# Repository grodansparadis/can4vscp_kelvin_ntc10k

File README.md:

-----

This project is part of the <a href="http://www.vscp.org">VSCP (Very Simple Control Protocol) project</a>. 

<hr>

# Kelvin NTC10K

This module is part of the [VSCP project](https://www.vscp.org).  It is free to use, modify and sell. The only thing we kindly ask is that improvements and extensions are contributed back to the project (at your will). This to make the project better for everyone. All design files is licensed under the [MIT license](https://en.wikipedia.org/wiki/MIT_License).

The full documentation for the module can be found [here](http://grodansparadis.github.io/can4vscp_kelvin_ntc10k/#/).

In this repository you find all development files for the Kelvin NTC10K module. The project together with the [Paris Relay Module](https://github.com/grodansparadis/can4vscp_paris) is the main examples for a VSCP implemention on a Microchip 18F PIC device.

## Abstract

Kelvin NTC10K is a temperature module that can handle six temperature sensors. One internal and five external.

The Kelvin NTC10KA module measures temperature. It measures temperatures in a wide range (depending on what sensors are used) and can achieve 0.1C accuracy with calibration. It does so by allowing connection of up to five external NTC temperature sensors and by measuring the temperature on the surface of the module itself. The measured temperature can be reported to other CAN4VSCP modules or to one or several servers so it can be collected in a database or visualized and analyzed in a diagram. The accuracy of the sensors can be increase further by calibration.

Temperature data can be presented by the module in Kelvin, Celsius or Fahrenheit.

Temperatures is reported automatically and it is possible to set alarms for high/low levels. Absolute low and high temperatures are collected and it is easy to construct autonomous and reliable temperature regulation systems.

NTC sensors has the advantage of being low cost, possible to get high accuracy from and ease of use with long cable runs. No calibration is usually needed if +-1 degree accuracy is OK.

The module fully adopts to the CAN4VSCP specification and can be powered directly over the bus with a 9-28V DC power source. It has a rich register set for configuration and any information events defined. It also have a decision matrix for easy dynamic event handling.

VSCP CAN modules are designed to work on a CAN4CAN bus which use ordinary RJ-45 connectors and is powered with 9-28V DC over the same cable. This means there is no need for a separate power cable. All that is needed is a CAT5 or better twisted pair cable. Buss length can be a maximum of 500 meters with drops of maximum 24 meters length (up to a total of 120 meters). As for all CAN4VSCP modules the communication speed is fixed at 125 kbps.

All VSCP modules contains information of there own setup, manual, hardware version, manufacturer etc. You just ask the module for the information you need and you will get it. When they are started up they have a default functionality that often is all that is needed to get a working setup. If the module have something to report it will send you an event and if it is setup to react on a certain type of event it will do it's work when you send event(s) to it. 

---

## Project files

### User manual
  * [User Manual](https://grodansparadis.github.io/can4vscp_kelvin_ntc10k/#)

### Schematic, PCB, 3D files etc
  * [Schematics reversion A](https://raw.githubusercontent.com/grodansparadis/can4vscp_accra/refs/heads/master/eagle/accra_sch_rev_A.png)
 * Hardware design files is made in [KiCad](https://kicad.org) and can be found in the `kicad` directory. Valid from reversion B of the hardware.
   * Gerber files for PCB production can be found in the `gerber` directory (in the `kicad` folder).
 * Eagle schema and board files for reversion A and B can be found in the `eagle` directory. They are no longer actively updated.

 ### Firmware

 The firmware is developed in [MPLAB X IDE](https://www.microchip.com/mplab/mplab-x-ide) using the [XC8 compiler](https://www.microchip.com/mplab/compilers).

  * Binary release files is available [here](https://github.com/grodansparadis/can4vscp_kelvin_ntc10k/releases)

### MDF - Module Description File(s)
  * [MDF file version: 1.2.0 Release date: 2015-02-18](http://www.eurosource.se/ntc10KA_3.xml)
  * [MDF file version: 1.1.0 Release date: 2014-12-24](http://www.eurosource.se/ntc10KA_2.xml)
  * [MDF file version: 1.0.0 Release date: 2012-02-24](http://www.eurosource.se/ntc10KA_1.xml)

### Support
If you need support, please open an issue in the [GitHub repository](https://github.com/grodansparadis/can4vscp_kelvin_ntc10k/issues).

### Buy a ready made modules
You can buy a ready made module from [Grodans Paradis](http://www.grodansparadis.com).

### Project related links
  * [VSCP project](https://www.vscp.org)
  * [VSCP Documentation site](https://docs.vscp.org/)
  * [VSCP Wiki](https://github.com/grodansparadis/vscp/wiki)

## Steps you should go through to adopt this file for your own VSCP project.

  * The frequency for your system may be different. This will affect the CAN bit rate settings which are defined in the biginning of the can18f.c file. Here you also find the filter/mask  defines if you need to change these. Timer0 is used as a 1 ms timer for the VSCP functionality. You should adopt the timer reload value in the main.h file to your system.

  * The GUID (Glocal Unique ID) is defined in the beginning of vscp.c This number should be different for each piece of equiment you produce. Regard it is as the device serial number. It can be moved to EEPROM if that is found more convinient. In that case the vscp_rcv_readreg  procedure in vscp.c also has to be changed.

  * The device URL is defined in the beginning of the vscp.c file. This is an URL without the initial "http://" that should point to a XML file that give information about your piece of equipment.

  * The manufacturer id is also defined in the beginning of the vscp.c file. You can use this id in any way you like.

In addition to this you may use different pins for the INIT button (RC0 today) and the status LED (RC1) today. Changes affect the main interrupt vector.

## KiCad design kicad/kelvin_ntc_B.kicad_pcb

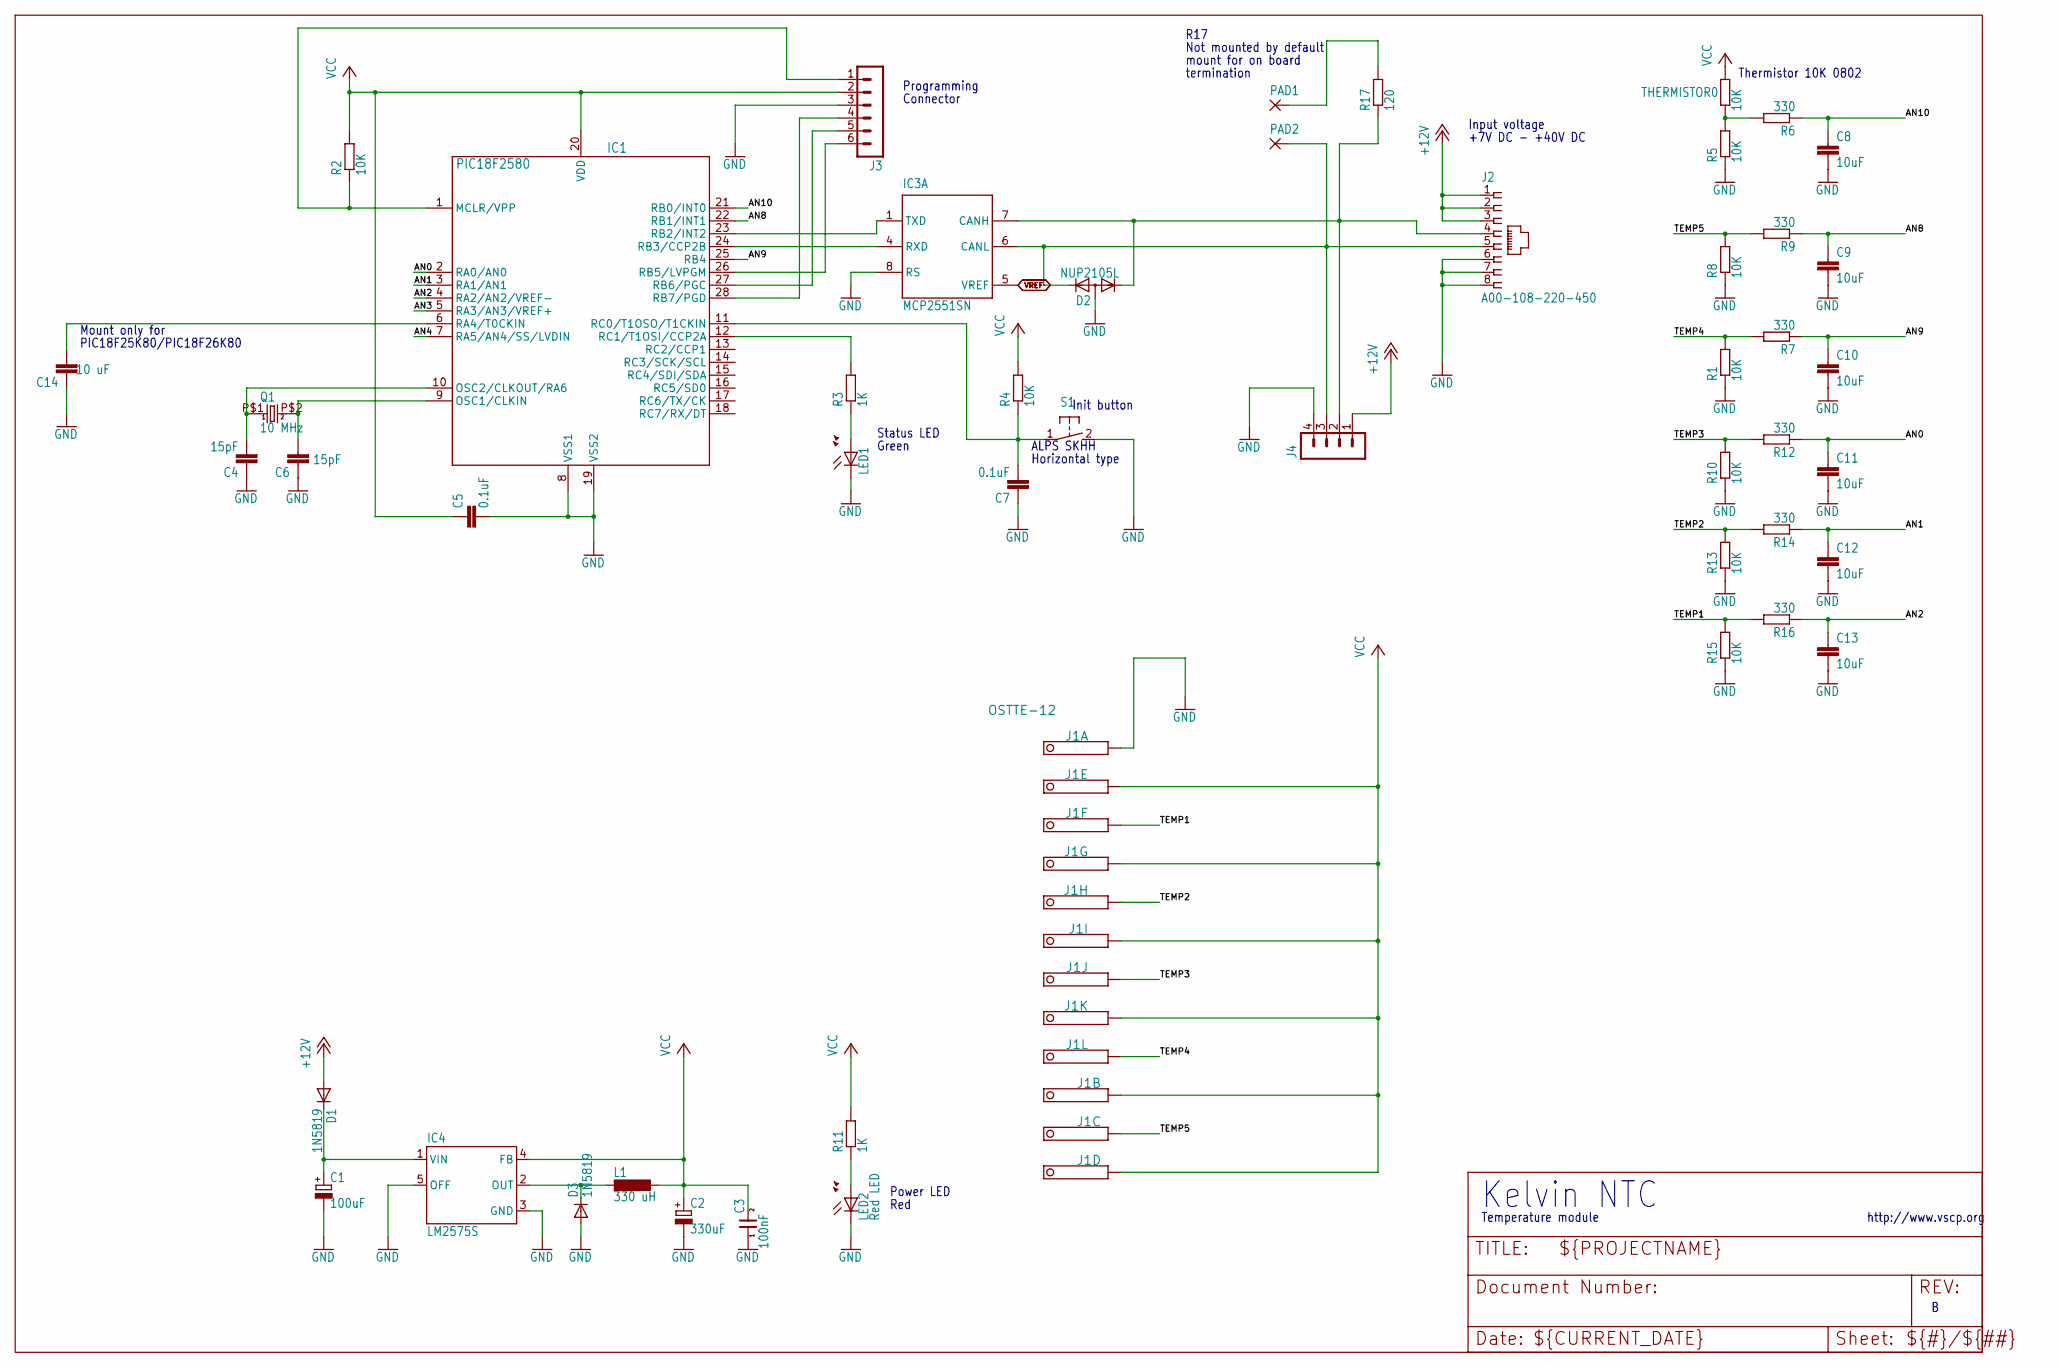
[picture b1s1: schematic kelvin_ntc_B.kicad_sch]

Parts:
C1: 100uF; PANASONIC_D
C2: 330uF; PANASONIC_D
C3: 100nF; 0805
C4, C6: 15pF; C0805
C5, C7: 0.1uF; C0805
C8, C9, C10, C11, C12, C13: 10uF; C0805
C14: 10 uF; C0805
D1, D3: 1N5819; SOD123
D2: NUP2105L; SOT23
IC1: PIC18F2580; SO28
IC3: MCP2551SN; SO-08
IC4: LM2575S; TO263-5
J1: OSTTE-12; PINHEAD-12
J2: A00-108-220-450; RJ-45
J3: MA06-1
J4: MA04-1
L1: 330 uH; DO3316P
LED1: LEDCHIP-LED0805; CHIP-LED0805
LED2: Red LED; CHIP-LED0805
PAD1, PAD2: 1,6/0,8; 1,6_0,8
Q1: 10 MHz; 9C
R1, R2, R4, R5, R8, R10, R13, R15: 10K; R0805
R3, R11: 1K; R0805
R6, R7, R9, R12, R14, R16: 330; R0805
R17: 120; R0805
S1: 31-XX; B3F-31XX
THERMISTOR0: 10K; R0805

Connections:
+12V: D1.A, J2.1, J2.2, J2.3, J4.1
AN0: C11.1, IC1.2 (RA0/AN0), R12.1
AN1: C12.1, IC1.3 (RA1/AN1), R14.1
AN2: C13.1, IC1.4 (RA2/AN2/VREF-), R16.1
AN3: IC1.5 (RA3/AN3/VREF+)
AN4: IC1.7 (RA5/AN4/SS/LVDIN)
AN8: C9.1, IC1.22 (RB1/INT1), R9.1
AN9: C10.1, IC1.25 (RB4), R7.1
AN10: C8.1, IC1.21 (RB0/INT0), R6.1
CANH: D2.1 (K1), IC3.7 (CANH), J2.4, J4.2, R17.1
CANL: D2.2 (K2), IC3.6 (CANL), J2.5, J4.3, PAD2.1
GND: C1.-, C2.-, C3.1, C4.1, C5.2, C6.1, C7.1, C8.2, C9.2, C10.2, C11.2, C12.2, C13.2, C14.1, D2.3 (A), D3.A, IC1.8 (VSS1), IC1.19 (VSS2), IC3.2 (VSS), IC3.8 (RS), IC4.3 (GND), IC4.5 (OFF), J1.1, J2.6, J2.7, J2.8, J3.3, J4.4, LED1.C, LED2.C, R1.1, R5.1, R8.1, R10.1, R13.1, R15.1, S1.2 (S)
unnamed: D3.C, IC4.2 (OUT), L1.1
unnamed: C4.2, IC1.10 (OSC2/CLKOUT/RA6), Q1.P$1 (1)
unnamed: C1.+, D1.C, IC4.1 (VIN)
unnamed: IC1.12 (RC1/T1OSI/CCP2A), R3.2
unnamed: LED1.A, R3.1
unnamed: C7.2, IC1.11 (RC0/T1OSO/T1CKIN), R4.1, S1.1
unnamed: C6.2, IC1.9 (OSC1/CLKIN), Q1.P$2 (2)
unnamed: R5.2, R6.2, THERMISTOR0.1
unnamed: C14.2, IC1.6 (RA4/T0CKIN)
unnamed: PAD1.1, R17.2
unnamed: IC1.1 (MCLR/VPP), J3.1, R2.1
unnamed: IC1.28 (RB7/PGD), J3.4
unnamed: IC1.27 (RB6/PGC), J3.5
unnamed: IC1.26 (RB5/LVPGM), J3.6
unnamed: LED2.A, R11.1
RXCAN: IC1.24 (RB3/CCP2B), IC3.4 (RXD)
TEMP1: J1.3, R15.2, R16.2
TEMP2: J1.5, R13.2, R14.2
TEMP3: J1.7, R10.2, R12.2
TEMP4: J1.9, R1.2, R7.2
TEMP5: J1.11, R8.2, R9.2
TXCAN: IC1.23 (RB2/INT2), IC3.1 (TXD)
VCC: C2.+, C3.2, C5.1, IC1.20 (VDD), IC3.3 (VDD), IC4.4 (FB), J1.2, J1.4, J1.6, J1.8, J1.10, J1.12, J3.2, L1.2, R2.2, R4.2, R11.2, THERMISTOR0.2
VREF: IC3.5 (VREF)

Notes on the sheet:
Init button
Connector
http://www.vscp.org
Mount only for
Input voltage
R17
Red
Thermistor 10K 0802
mount for on board
termination
Kelvin NTC
Horizontal type
Programming
Status LED
Not mounted by default
Power LED
+7V DC - +40V DC
Green
PIC18F25K80/PIC18F26K80
Temperature module
ALPS SKHH

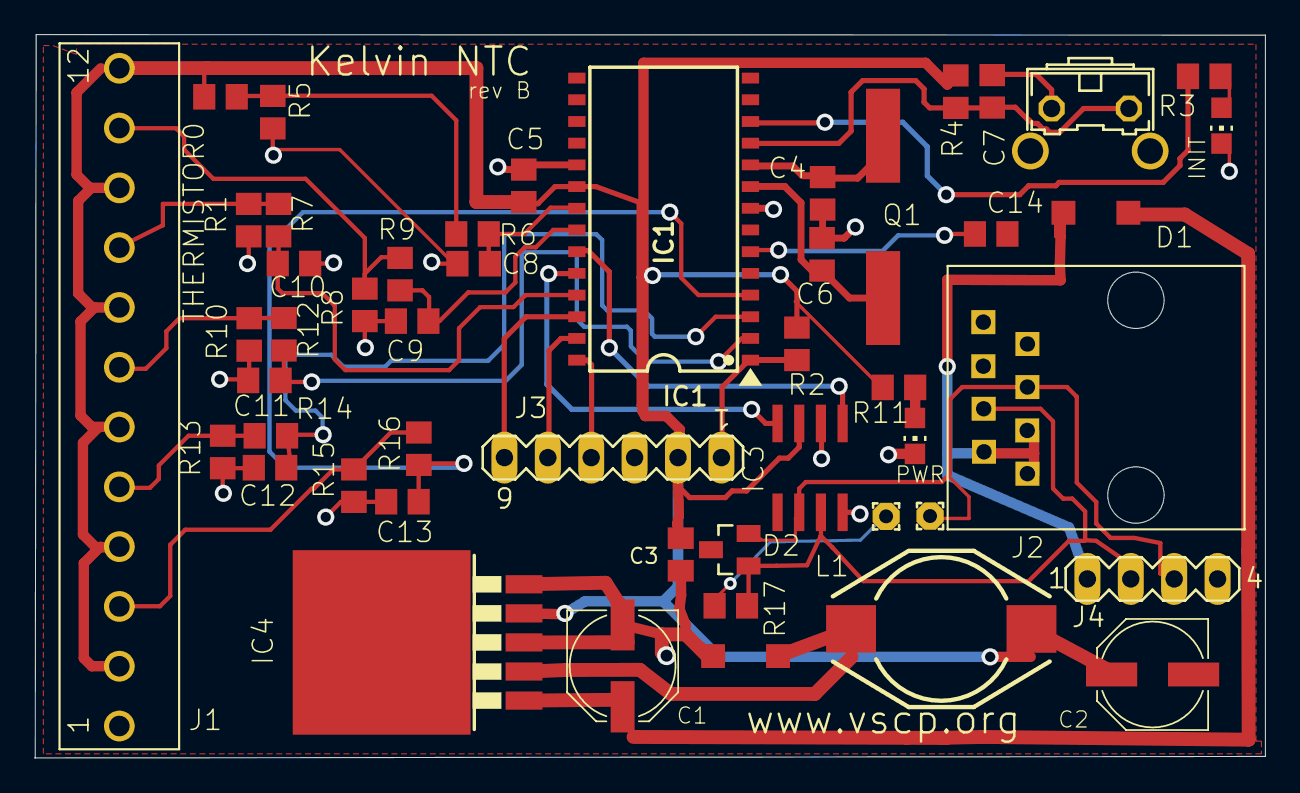
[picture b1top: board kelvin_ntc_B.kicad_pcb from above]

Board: 6 copper layers, 72.0 x 42.3 mm, 49 parts (0 on the bottom side), 33 nets.

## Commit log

2015-02-12 Moved Kelvin NTC10KA to public repository
2015-02-14 Renamed
2015-02-14 Removed some dirt
2015-02-14 Removed unused folder
2015-02-18 Moved calibration registers to page 1 and removed indexed storage
2015-02-18 Added default values to mdf. Calibration values are now stored flat
2015-02-18 Fixed error in absolute low/high value registers
2015-03-03 Added missing update of vscp_configtimer
2015-03-04 Fixed typo
2015-03-24 Version 1.2.1 fixes.
2015-03-24 Added release firmware folder
2015-03-24 Distro files
2015-07-12 Edit
2015-07-27 Fixed problem with send timeout
2015-08-17 Released eagle design files
2015-08-17 Changed license to MIT
2015-09-09 Wrong (old) schema was previously uploaded. Fixed now.
2015-09-12 Added missing files
2015-09-14 Release 1.2.2
2015-09-14 Removed some invalid characters from xml
2015-09-28 Sensor is read wrongly in register view. Fixed
2015-11-11 Added the manual that was in wrong location (Paris)
2015-11-12 Replaced the readme file
2015-11-12 Added missing image file
2015-11-13 Added firmware readme
2015-11-22 Color for abstraction low sensor alarm for sensor 0 corrected
2015-11-24 Moved limit and alarm tests to one second work where they belong.
2015-11-25 Now turn of CAN i/f before going into bootloader.
2015-11-26 Fixed problem with low/high limits with negative values. Also limits now are in degrees as is hysteresis as well.
2015-12-17 Added images
2016-02-04 Temperature calibration value was calulated in the wrong way.
2016-03-06 C14 should be 10K
2016-03-08 Now builds with 1.6 firmware
2016-03-08 Fixed copyright info
2016-03-23 Fixed bug in control byte write routine
2016-03-23 Preparing for new release
2016-03-23 Updated project files
2016-03-23 Fixed XML build error
2016-03-23 Version 1.2.4
2016-03-23 Version 1.2.5
2016-03-29 Raw A/D register values was displayed in wrong order. Fixed.
2016-03-30 Adopted for PIC18F26K80
2016-04-08 Fixed default value for unit
2016-04-08 Fixed mdf bugs in control registors refering to sensor 0 on all
2016-04-08 Fixed reference to sensor 0 in low/hig registers
2016-04-08 Fixed some minor typos
2016-04-19 RA4 set to input to prevent collision with VCAP circuits in PIC18F2580. Brown out raised to maximum (3V & 4.6V). Valuable input from Anders Forsgren, AJE Electronics AB.
2016-05-04 Added new link to bit timing
2018-11-06 Updated dates
2019-12-09 Updated to work on new compiler
2020-05-04 Moved manual to docsify
2020-05-15 init timer is now 2500 ms instead of 250 ms
2020-05-15 Updated firmware
2025-02-09 Added initial text for new manual
2025-02-09 Changed links
2025-02-16 Fixed cover
2025-02-17 Updated README with correct links
2025-02-17 Removed sidebar logo
2025-02-17 Removed old pdf manual
2025-02-17 Added logo to cover
2025-02-17 Added .nojekyll
2025-02-17 Removed lyx
2025-02-17 Addded config info
2025-08-18 Converted schema to kicad
2025-09-05 Fixed some typos
2025-09-05 Changed liunk to manual
2025-09-05 Retired old manual
